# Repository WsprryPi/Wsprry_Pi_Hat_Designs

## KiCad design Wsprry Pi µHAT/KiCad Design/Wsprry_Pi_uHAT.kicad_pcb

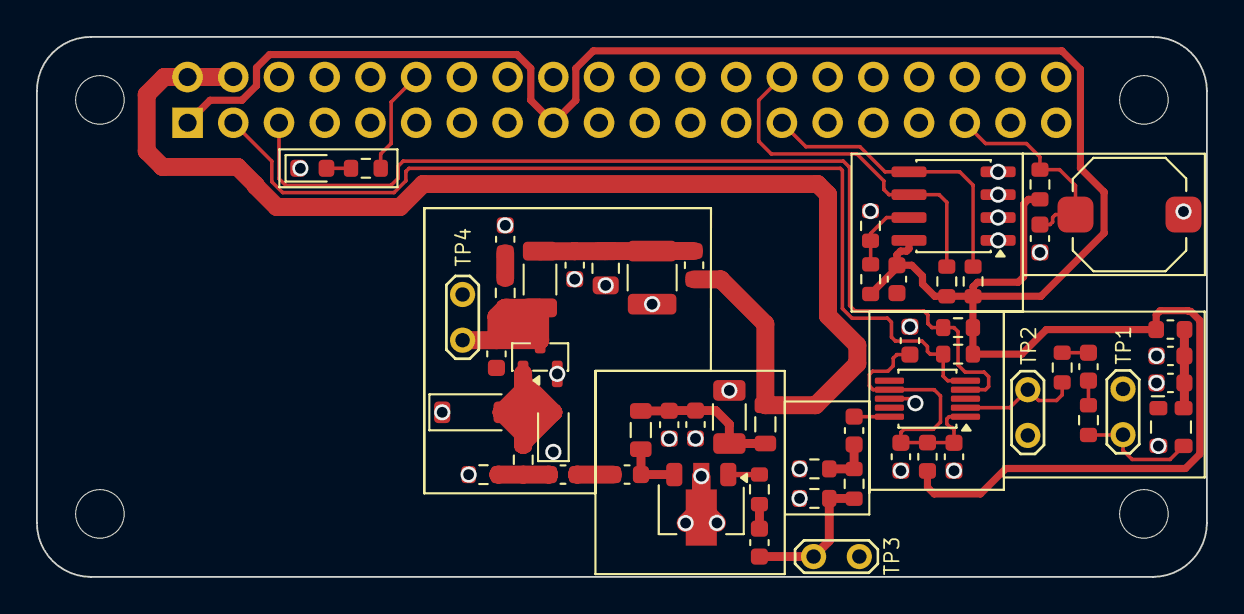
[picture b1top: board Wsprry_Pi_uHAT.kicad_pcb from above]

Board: 2 copper layers, 65.0 x 30.0 mm, 61 parts (1 on the bottom side), 30 nets.

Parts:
C1, C5, C7, C10, C20: 0.1µF; C_0603_1608Metric
C2: 0.1uF; C_0603_1608Metric
C3: 1.0uF; C_0603_1608Metric
C4: 1nF; C_0603_1608Metric
C6, C9: 1.0µF; C_0603_1608Metric
C8: 1uF; C_0603_1608Metric
C11: 1µF; C_0603_1608Metric
C12: 10µF; C_1206_3216Metric
C13: 0.1F; C_0603_1608Metric
C14: 100n; C_0603_1608Metric
C15: 22nF; C_0603_1608Metric
C16: 22pF; C_0603_1608Metric
C17: 100pF; C_0603_1608Metric
C18: 10µF; C_1210_3225Metric
C19: 1.0µF; C_0805_2012Metric
D1: RED; LED_0603_1608Metric
D2: BAT54J; D_SOD-323F
D3: 5.1V; D_SOD-123
FB1, FB2: 600Ω@100MHz; L_0603_1608Metric
FB3: 600Ω100MHz; L_0805_2012Metric
FB4: 600Ω@100MHZ; L_0603_1608Metric
J1: Raspberry Pi Header; PinSocket_2x20_P2.54mm_Vertical
L1: 2.2µH; L_0805_2012Metric
L2: 2.2µH; L_1206_3216Metric
MH1, MH2, MH3, MH4: MountingHole_2.7mm_M2.5
Q1: AO3400A; SOT-23
R1: 270Ω; R_0603_1608Metric
R2: 10kΩ; R_0603_1608Metric
R3: 33Ω; R_0603_1608Metric
R4, R7, R13: 0Ω; R_0603_1608Metric
R5, R6: 2K2; R_0603_1608Metric
R8, R10: 292Ω; R_0603_1608Metric
R9: 17.6Ω; R_0603_1608Metric
R11: 47kΩ; R_0603_1608Metric
R12, R14: 3.9K; R_0603_1608Metric
R15: 49.9Ω; R_0603_1608Metric
R16: 10Ω; R_0603_1608Metric
R17: 100Ω; R_0603_1608Metric
SW1: SW_Push; SW_Push_1TS009xxxx-xxxx-xxxx_6x6x5mm
TP1: TP_XRAW; TestPoint_2Pads_Pitch2.54mm_Drill0.8mm
TP2: TP_XREF; TestPoint_2Pads_Pitch2.54mm_Drill0.8mm
TP3: TP_PAD_OUT; TestPoint_2Pads_Pitch2.54mm_Drill0.8mm
TP4: TP_PAOUT; TestPoint_2Pads_Pitch2.54mm_Drill0.8mm
U1: GVA-84; SOT-89-3
U2: 24LC128; SOIC-8_3.9x4.9mm_P1.27mm
Y1: ATX-11-F-27.000MHZ-F05-T; Oscillator_SMD_SeikoEpson_TG2520SMN-xxx-xxxxxx-4Pin_2.5x2.0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
Y2: Si5351A-B-GT; MSOP-10_3x3mm_P0.5mm

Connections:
3V3: C14.2, FB1.2, FB2.1, J1.1 (3V3), J1.17 (3V3), R2.1, R5.2, R6.2, R12.1, R13.2, R14.1, U2.8 (VCC)
5V: FB3.2, FB4.1, J1.2 (5V), J1.4 (5V)
/HAT+ EEPROM/ID_SCL: J1.28 (ID_SCL), R14.2, U2.6 (SCL)
/HAT+ EEPROM/ID_SDA: J1.27 (ID_SDA), R12.2, U2.5 (SDA)
/Raspberry Pi Header/PI_SCL: J1.5 (I2C1_SCL), R5.1, Y2.4 (SCL)
/Raspberry Pi Header/PI_SDA: J1.3 (I2C1_SDA), R6.1, Y2.5 (SDA)
/Raspberry Pi Header/PI_SHUTDOWN: C1.1, J1.35 (GPIO19), R2.2, SW1.1
/Raspberry Pi Header/PI_TXLED: J1.12 (GPIO18), R1.2
/Si5153 Chain/3dB Pi Pad/3DB_PAD_OUT: C8.1, R9.2, R10.1, TP3.1
/Si5153 Chain/3dB Pi Pad/CLOCK_IN: C13.1, Y2.10 (CLK0)
/Si5153 Chain/Clock/XTAL_IN: R4.2, TP2.1, Y2.2 (XA)
/Si5153 Chain/Final PA/MMIC_IN: C11.1, C15.1
/Si5153 Chain/Final PA/PA_OUT: C16.2, L2.2, Q1.3 (D), R17.1, TP4.1
GND: C1.2, C2.1, C3.1, C5.2, C6.2, C7.2, C9.2, C10.2, C12.2, C14.1, C16.1, C17.2, C18.2, C19.2, C20.2, D1.1 (K), D2.1 (K), D3.1 (K), J1.9 (GND), J1.25 (GND), J1.39 (GND), Q1.2 (S), R8.2, R10.2, R11.2, R15.2, SW1.2, TP1.2, TP2.2, TP3.2, TP4.2, U1.2 (GND), U2.1 (A0), U2.2 (A1), U2.3 (A2), U2.4 (GND), Y1.2 (GND), Y2.8 (GND)
unnamed: C4.1, R3.2
unnamed: C4.2, R4.1
unnamed: C8.2, R7.1
unnamed: C9.1, C10.1, C12.1, FB3.1, L1.1
unnamed: C11.2, L1.2, U1.3
unnamed: C13.2, R8.1, R9.1
unnamed: C15.2, R15.1, R16.1
unnamed: C17.1, R17.2
unnamed: C18.1, C19.1, C20.1, FB4.2, L2.1
unnamed: D1.2 (A), R1.1
unnamed: D2.2 (A), D3.2 (A), Q1.1 (G), R16.2
unnamed: R7.2, U1.1
unnamed: R11.1, R13.1, U2.7 (WP)
unnamed: R3.1, TP1.1, Y1.3 (OUT)
unnamed: C2.2, C3.2, FB1.1, Y1.4 (Vcc)
unnamed: C5.1, C6.1, C7.1, FB2.2, Y2.1 (VDD), Y2.7 (VDDO)

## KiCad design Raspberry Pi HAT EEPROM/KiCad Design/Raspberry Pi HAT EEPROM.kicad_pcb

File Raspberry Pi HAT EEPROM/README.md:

# HAT ID EEPROM Circuit

## Overview

This block implements a **Raspberry Pi HAT identification EEPROM** used to automatically identify
the attached board at boot time.

The circuit allows the Raspberry Pi to:

- Detect the presence of the HAT
- Read board identification and configuration data
- Automatically configure GPIO functions
- Optionally load Linux drivers based on the HAT descriptor

This block is **non-RF** and operates independently of the RF signal chain.

---

## Intent and Design Goals

Raspberry Pi HAT designs rely on a small I²C EEPROM connected to the reserved **ID_SD** and **ID_SC** pins.
At boot, the Raspberry Pi firmware interrogates this EEPROM to determine board identity and capabilities.

This circuit is designed to:

- Fully comply with the Raspberry Pi HAT specification
- Require no configuration or tuning in normal operation
- Protect the EEPROM contents after programming
- Remain electrically isolated from the RF circuitry

---

## Circuit Description

The circuit consists of a dedicated I²C EEPROM with pull-up resistors and optional write protection.

### Functional sections

- **EEPROM device (U2)**  
  Stores the HAT identification data.

- **I²C pull-up resistors (R1, R2)**  
  Provide the required pull-ups on SDA and SCL for the ID bus.

- **Local decoupling capacitor (C1)**  
  Stabilizes the EEPROM supply during I²C transactions.

- **Write-protect jumper (JP1)**  
  Allows permanent write protection after programming.

---

## Component Selection Rationale

### EEPROM

- **CAT24C32 (or compatible 24C32 device)**
  - I²C-compatible EEPROM
  - Adequate capacity for HAT descriptor data
  - Widely available and low cost

Address pins A0–A2 are left unconnected to select the default address required by the HAT specification.

### Pull-up resistors

- **R1, R2 = 3.9 kΩ**
  - Compliant with Raspberry Pi HAT electrical requirements
  - Ensures reliable I²C signaling at boot

### Decoupling capacitor

- **C1 = 0.1 µF**
  - Local supply stabilization
  - Placed close to the EEPROM device

### Write-protect jumper

- **JP1**
  - Open: EEPROM is writable
  - Bridged: Write protection enabled (WP tied high)

---

## Performance Expectations

- Reliable EEPROM detection during Raspberry Pi boot
- No interaction with or impact on RF circuit performance
- Stable operation across normal temperature and voltage ranges

This circuit performs no time-critical or high-speed function.

---

## Integration Notes

### Placement

- Place the EEPROM close to the Raspberry Pi header.
- Keep SDA and SCL traces short and routed together.
- Avoid routing RF signals near the ID bus traces.

### Programming

- Program the EEPROM prior to final assembly or in-circuit before enabling write protection.
- After verification, bridge **JP1** to prevent accidental overwrites.

### Signal Chain Context

```text
Raspberry Pi ID Bus (ID_SD, ID_SC)
    → HAT ID EEPROM
    → Boot-Time Board Identification
```

---

## Testing and Validation

Recommended checks:

- Confirm EEPROM is detected at boot
- Verify correct HAT identification using Raspberry Pi tools
- Confirm EEPROM is not writable after WP is enabled

No calibration or tuning is required.

---

## Summary

This HAT ID EEPROM circuit provides standards-compliant board identification for Raspberry Pi HAT designs.
It enables automatic configuration at boot while remaining isolated from the RF circuitry.
Once programmed and write-protected, it requires no further interaction.

---

## Reference

Raspberry Pi Ltd. *Raspberry Pi HAT+ Specification: A Guide to Designing Hardware-Attached-on-Top of a Raspberry Pi.* Build date: 2024-12-05. Build version: 6df06cc-clean. [https://datasheets.raspberrypi.com/hat/hat-plus-specification.pdf](https://datasheets.raspberrypi.com/hat/hat-plus-specification.pdf)

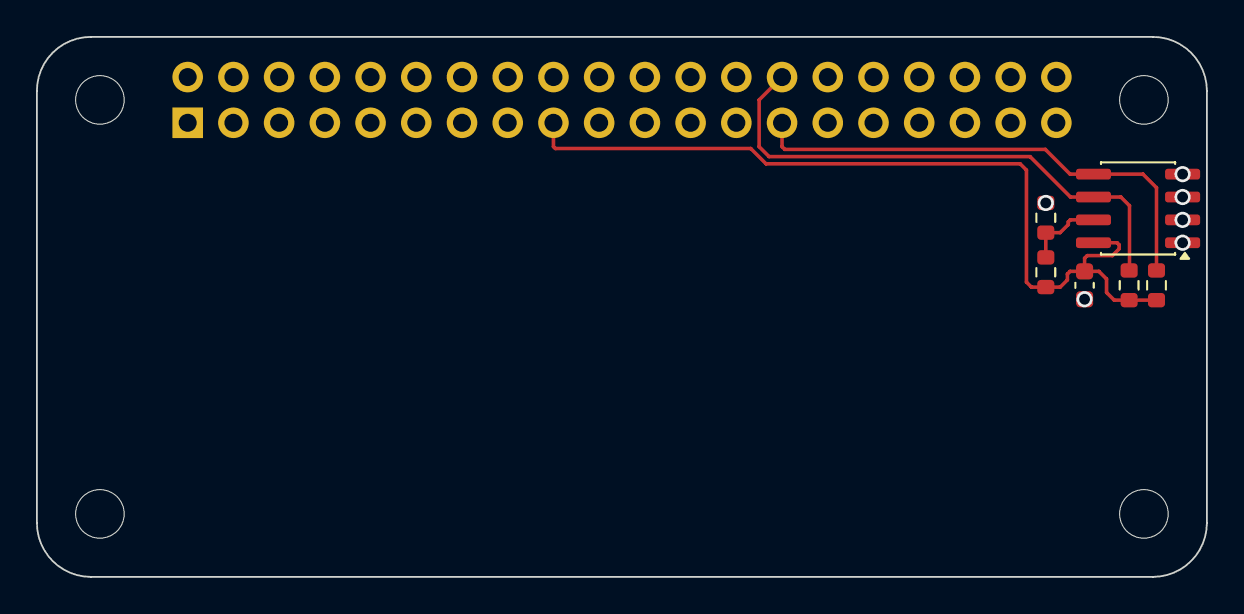
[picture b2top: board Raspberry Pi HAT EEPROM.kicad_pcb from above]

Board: 2 copper layers, 65.0 x 30.0 mm, 11 parts (1 on the bottom side), 5 nets.

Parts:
C1: 100n; C_0603_1608Metric
J1: Raspberry Pi Header; PinSocket_2x20_P2.54mm_Vertical
MH1, MH2, MH3, MH4: MountingHole_2.7mm_M2.5
R1, R2: 3.9K; R_0603_1608Metric
R3: 47kΩ; R_0603_1608Metric
R4: 0Ω; R_0603_1608Metric
U1: 24LC128; SOIC-8_3.9x4.9mm_P1.27mm

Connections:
/ID EEPROM/ID_3V3: C1.1, J1.1 (3V3), J1.17 (3V3), R1.1, R2.1, R4.2, U1.8 (VCC)
/ID EEPROM/ID_GND: C1.2, J1.6 (GND), J1.9 (GND), J1.14 (GND), J1.20 (GND), J1.25 (GND), J1.30 (GND), J1.34 (GND), J1.39 (GND), R3.2, U1.1 (A0), U1.2 (A1), U1.3 (A2), U1.4 (GND)
/ID EEPROM/ID_SCL: J1.28 (SDA0), R2.2, U1.6 (SCL)
/ID EEPROM/ID_SDA: J1.27 (SDA0), R1.2, U1.5 (SDA)
unnamed: R3.1, R4.1, U1.7 (WP)

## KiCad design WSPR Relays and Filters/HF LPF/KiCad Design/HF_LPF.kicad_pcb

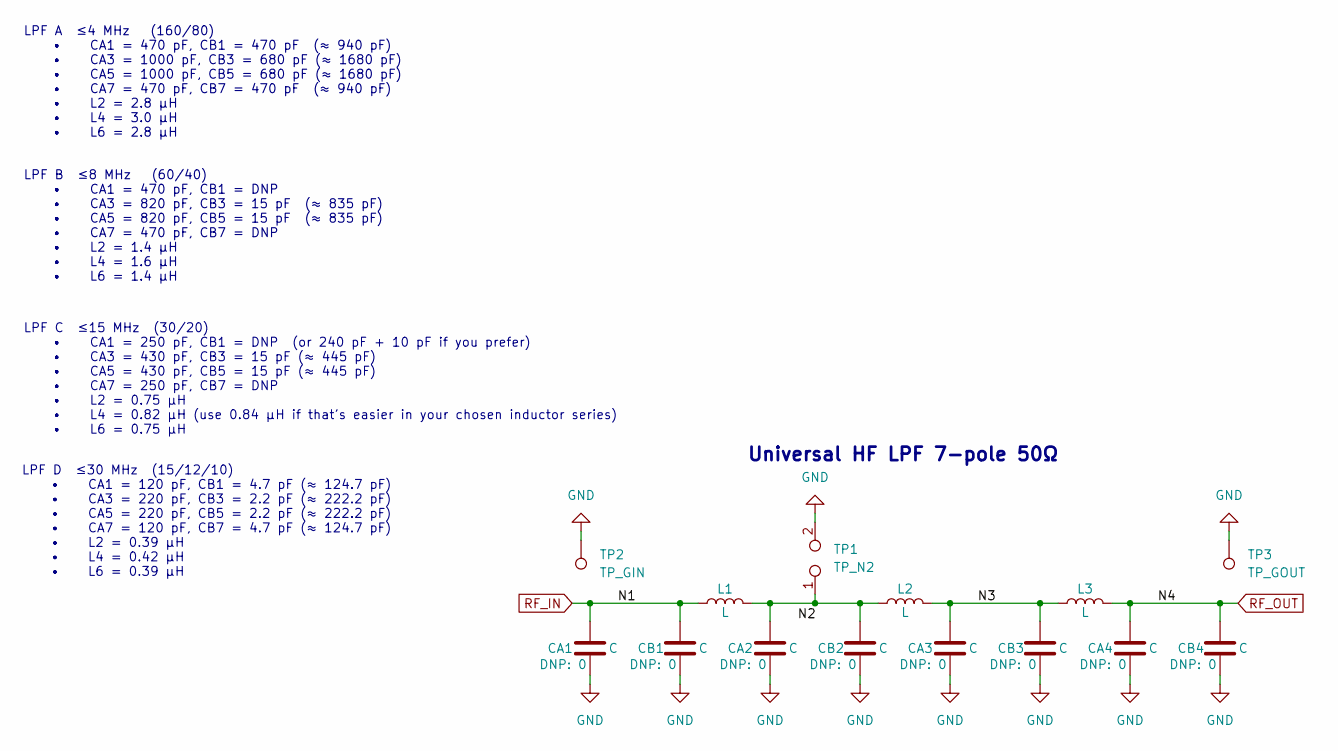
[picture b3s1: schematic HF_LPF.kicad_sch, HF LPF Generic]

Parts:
CA1, CA2, CA3, CA4: C; C_0805_2012Metric
CB1, CB2, CB3, CB4: C; C_0805_2012Metric
L1, L2, L3: L; L_1206_3216Metric
TP1: TP_N2; TestPoint_2Pads_Pitch2.54mm_Drill0.8mm
TP2: TP_GIN; TestPoint_Pad_1.0x1.0mm
TP3: TP_GOUT; TestPoint_Pad_1.0x1.0mm

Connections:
/N3: CA3.1, CB3.1, L2.2, L3.1
GND: CA1.2, CA2.2, CA3.2, CA4.2, CB1.2, CB2.2, CB3.2, CB4.2, TP1.2, TP2.1, TP3.1
unnamed: CA2.1, CB2.1, L1.2, L2.1, TP1.1
RF_IN: CA1.1, CB1.1, L1.1
RF_OUT: CA4.1, CB4.1, L3.2

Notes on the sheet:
Universal HF LPF 7-pole 50Ω
LPF C ≤15 MHz (30/20) • CA1 = 250 pF, CB1 = DNP (or 240 pF + 10 pF if you prefer) • CA3 = 430 pF, CB3 = 15 pF (≈ 445 pF) • CA5 = 430 pF, CB5 = 15 pF (≈ 445 pF) • CA7 = 250 pF, CB7 = DNP • L2 = 0.75 µH • L4 = 0.82 µH (use 0.84 µH if that's easier in your chosen inductor series) • L6 = 0.75 µH
LPF D ≤30 MHz (15/12/10) • CA1 = 120 pF, CB1 = 4.7 pF (≈ 124.7 pF) • CA3 = 220 pF, CB3 = 2.2 pF (≈ 222.2 pF) • CA5 = 220 pF, CB5 = 2.2 pF (≈ 222.2 pF) • CA7 = 120 pF, CB7 = 4.7 pF (≈ 124.7 pF) • L2 = 0.39 µH • L4 = 0.42 µH • L6 = 0.39 µH
LPF B ≤8 MHz (60/40) • CA1 = 470 pF, CB1 = DNP • CA3 = 820 pF, CB3 = 15 pF (≈ 835 pF) • CA5 = 820 pF, CB5 = 15 pF (≈ 835 pF) • CA7 = 470 pF, CB7 = DNP • L2 = 1.4 µH • L4 = 1.6 µH • L6 = 1.4 µH
LPF A ≤4 MHz (160/80) • CA1 = 470 pF, CB1 = 470 pF (≈ 940 pF) • CA3 = 1000 pF, CB3 = 680 pF (≈ 1680 pF) • CA5 = 1000 pF, CB5 = 680 pF (≈ 1680 pF) • CA7 = 470 pF, CB7 = 470 pF (≈ 940 pF) • L2 = 2.8 µH • L4 = 3.0 µH • L6 = 2.8 µH

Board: 2 copper layers, 14 parts (0 on the bottom side), 5 nets, no tracks yet.

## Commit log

2026-02-09 Set up hierarchical sheets
2026-02-14 Notionally complete through PA
